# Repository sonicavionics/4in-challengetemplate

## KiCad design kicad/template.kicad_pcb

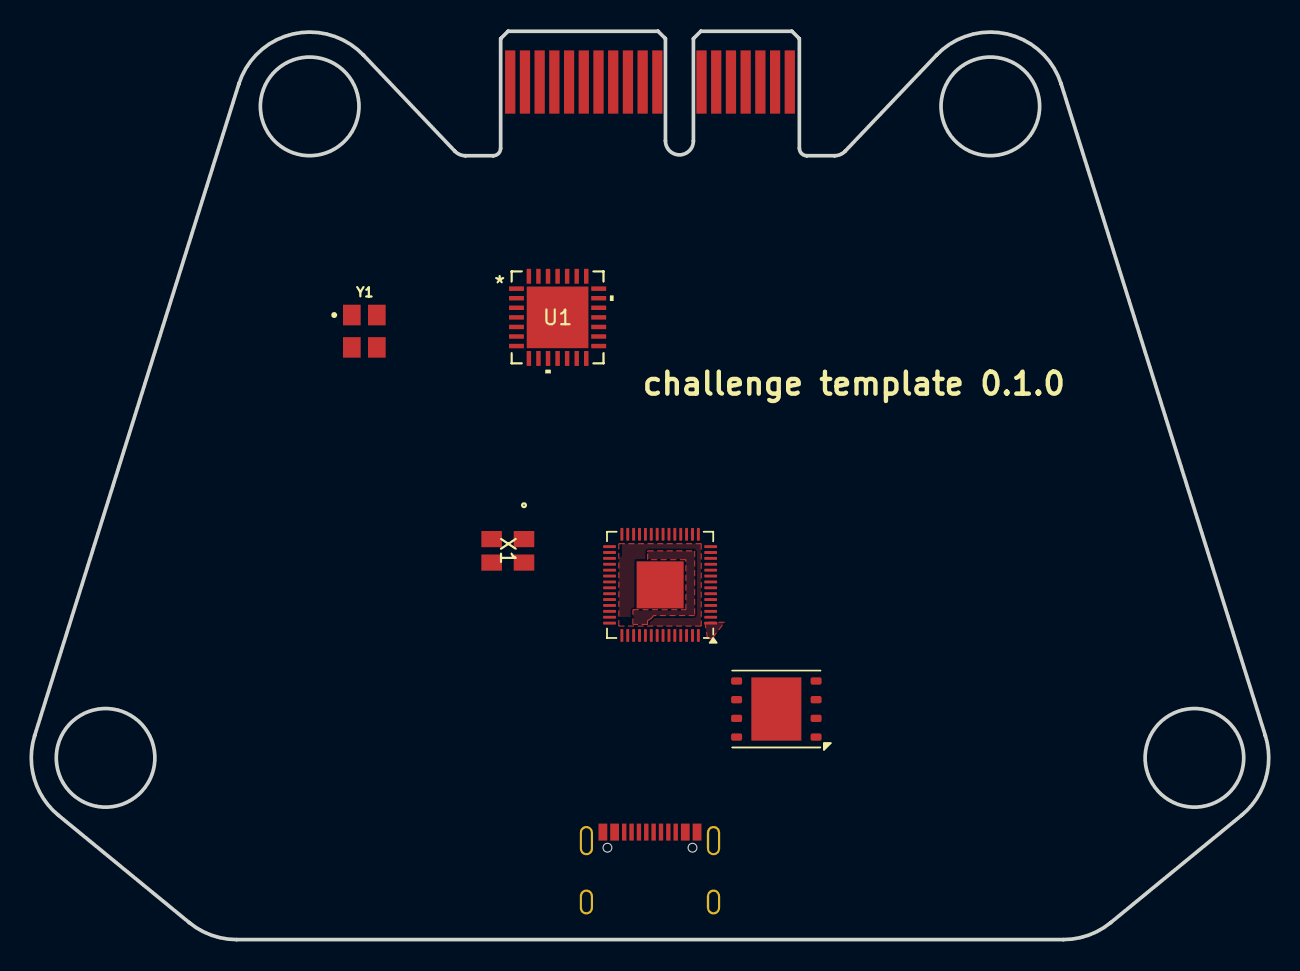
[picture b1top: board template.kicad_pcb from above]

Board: 2 copper layers, 84.1 x 61.7 mm, 7 parts (1 on the bottom side), 9 nets, no tracks yet.

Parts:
J1: Bus_PCI_Express_x1; BUS_PCIexpress_x1
J6: USB_C_Receptacle_USB2.0_16P; USB_C_Receptacle_Palconn_UTC16-G
U1: MCP25625T-E/ML; QFN28_6X6MC_MCH
U2: RP2040; QFN-56-1EP_7x7mm_P0.4mm_EP3.2x3.2mm
U4: W25Q128JVP; WSON-8-1EP_6x5mm_P1.27mm_EP3.4x4.3mm
X1: ABM8-272-T3; ABM8-272-T3_ABR
Y1: X322516MLB4SI; OSC_X322516MLB4SI

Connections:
+3.3V: J1.A9 (+3.3V), J1.A10 (+3.3V), J1.A11 (~PERST), J1.B9 (JTAG1), J1.B10 (3.3Vaux), J1.B11 (~WAKE)
+5V: J1.A12 (GND), J1.A13 (REFCLK+), J1.A14 (REFCLK-), J1.B12 (RSVD), J1.B13 (GND), J1.B14 (PETp0)
+BAT: J1.A16 (PERp0), J1.A17 (PERn0), J1.A18 (GND), J1.B16 (GND), J1.B17 (~PRSNT2), J1.B18 (GND)
GND: J1.A4 (GND), J1.A5 (JTAG2), J1.A6 (JTAG3), J1.A7 (JTAG4), J1.B1 (+12V), J1.B2 (+12V), J1.B3 (+12V), J1.B4 (GND), J1.B5 (SMCLK), J1.B6 (SMDAT), J1.B7 (GND), J6.A1 (GND), J6.A12 (GND), J6.B1 (GND), J6.B12 (GND), J6.S1 (SHIELD)
unnamed: J6.A6 (D+), J6.B6 (D+)
unnamed: J6.A7 (D-), J6.B7 (D-)
unnamed: U2.23 (DVDD), U2.50 (DVDD)
unnamed: U2.1 (IOVDD), U2.10 (IOVDD), U2.22 (IOVDD), U2.33 (IOVDD), U2.42 (IOVDD), U2.49 (IOVDD)
unnamed: Y1.2, Y1.4

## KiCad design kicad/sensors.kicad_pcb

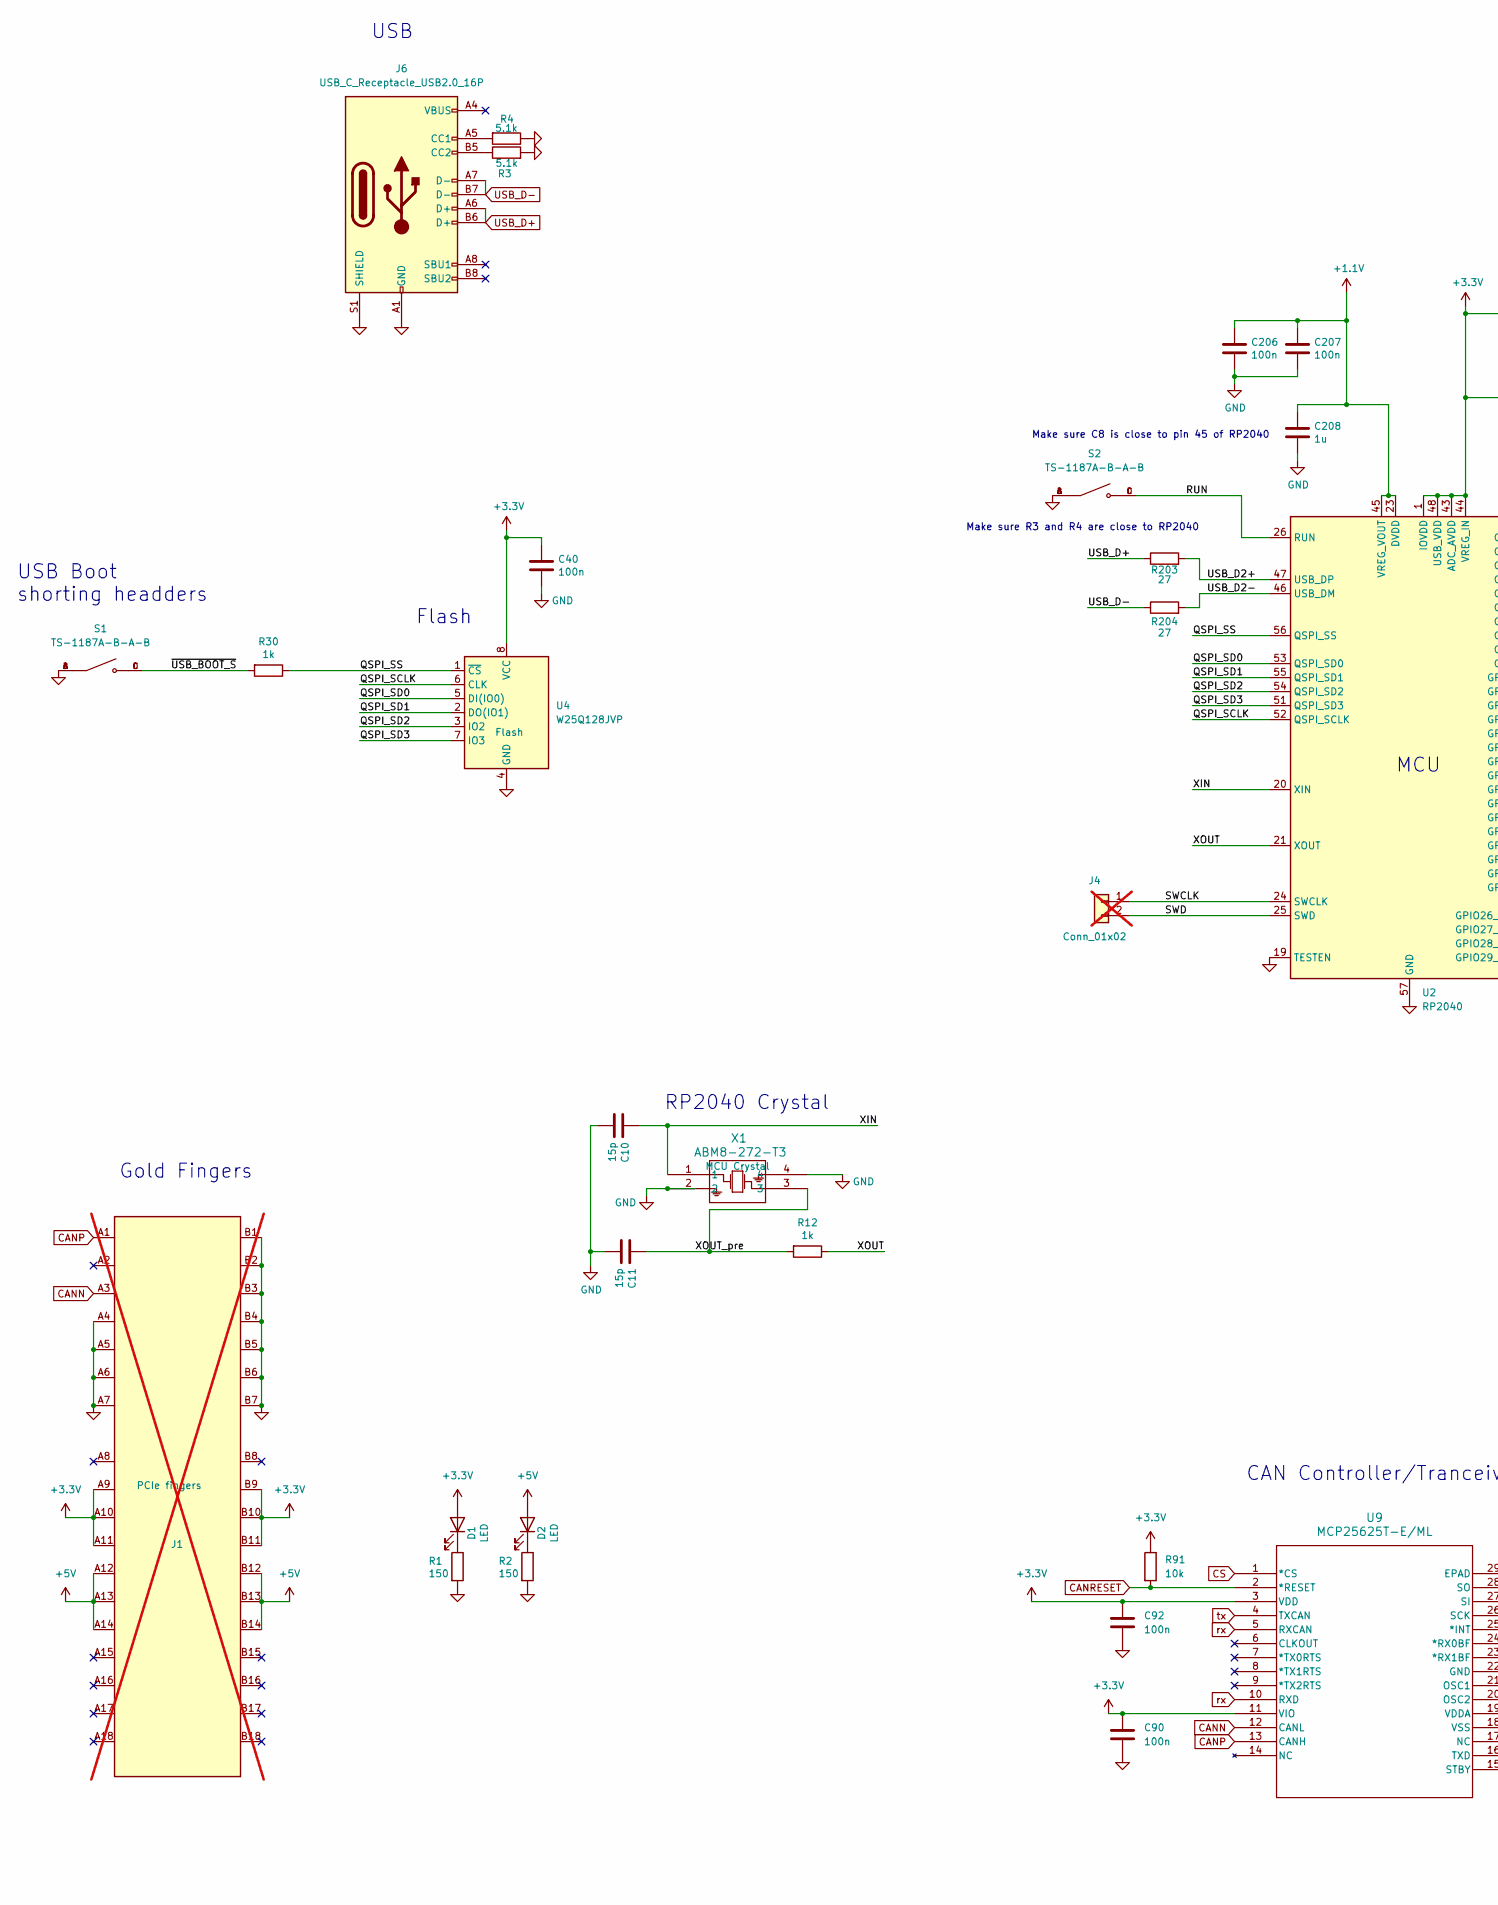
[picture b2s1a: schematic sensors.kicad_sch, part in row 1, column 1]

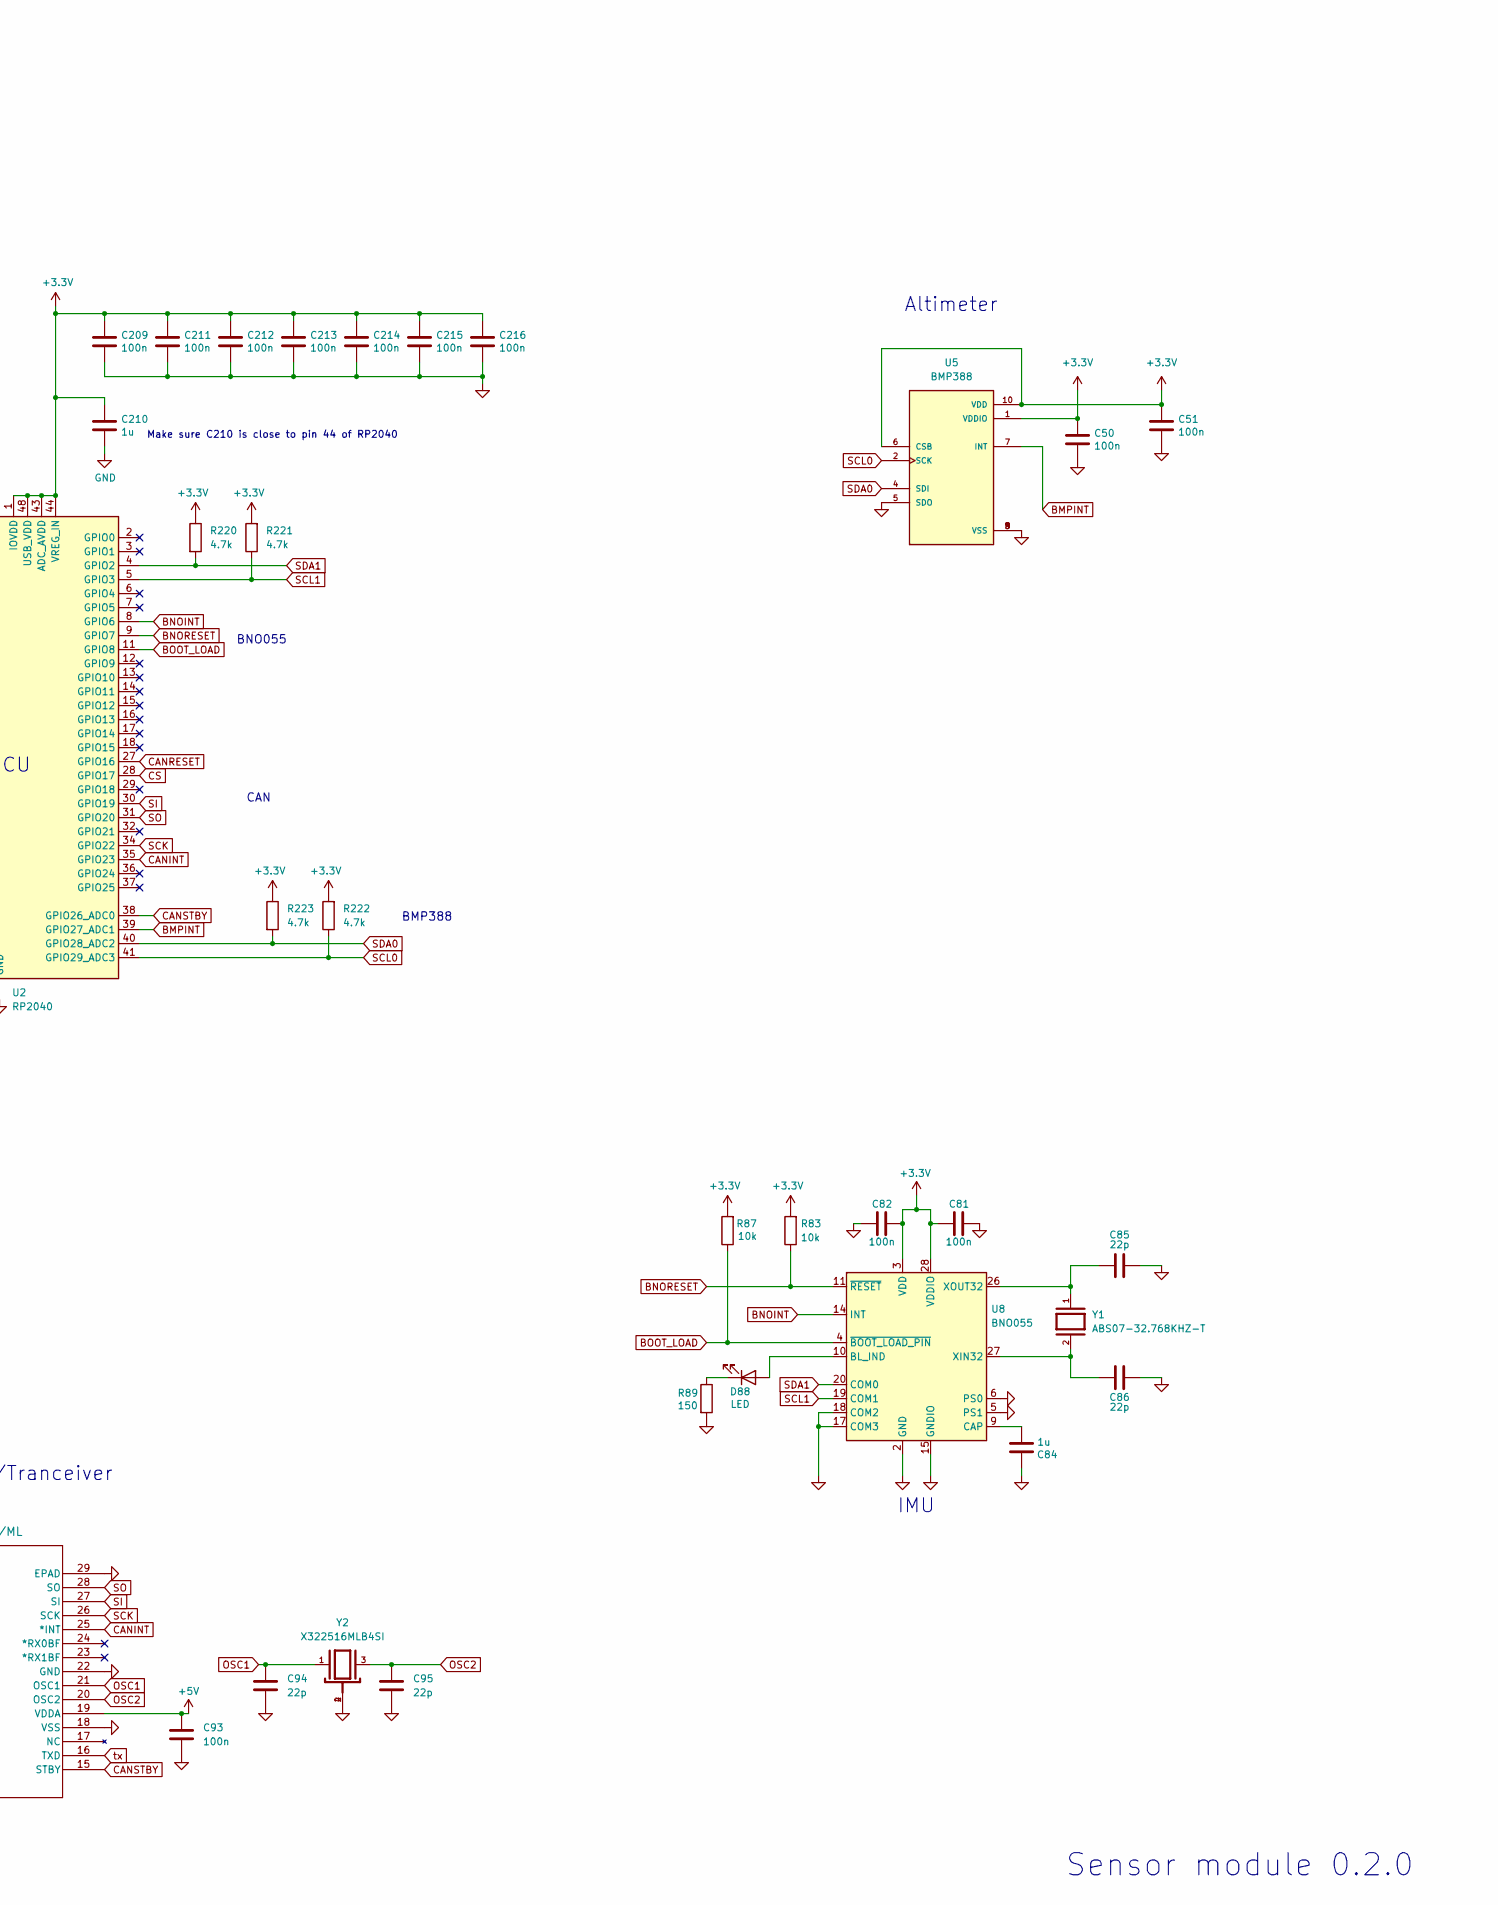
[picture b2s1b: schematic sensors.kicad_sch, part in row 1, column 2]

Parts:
C10, C11: 15p; C_0402_1005Metric; LCSC Part # C1548
C40, C50, C51, C81, C82, C90, C92, C93, C206, C207, C209, C211, C212, C213, C214, C215, C216: 100n; C_0402_1005Metric; LCSC Part # C307331
C84, C208, C210: 1u; C_0402_1005Metric; LCSC Part # C52923
C85, C86, C94, C95: 22p; C_0402_1005Metric; LCSC Part # C1555
D1, D2, D88: LED; LED_0603_1608Metric; LCSC Part # C2286
J1: Bus_PCI_Express_x1; BUS_PCIexpress_x1; LCSC Part # n/a; not fitted
J4: Conn_01x02; PinHeader_1x02_P2.54mm_Vertical; LCSC Part # n/a; not fitted
J6: USB_C_Receptacle_USB2.0_16P; USB_C_Receptacle_Palconn_UTC16-G; LCSC Part # C2765186
R1, R2, R89: 150; R_0603_1608Metric; LCSC Part # C22808
R3, R4: 5.1k; R_0402_1005Metric; LCSC Part # C25905
R12, R30: 1k; R_0402_1005Metric; LCSC Part # C11702
R83, R87, R91: 10k; R_0402_1005Metric; LCSC Part # C25744
R203, R204: 27; R_0402_1005Metric; LCSC Part # C25100
R220, R221, R222, R223: 4.7k; R_0402_1005Metric; LCSC Part # C25900
S1, S2: TS-1187A-B-A-B; SW_TS-1187A-B-A-B; PARTREV A0; LCSC Part # C318884
U2: RP2040; QFN-56-1EP_7x7mm_P0.4mm_EP3.2x3.2mm; LCSC C2040
U4: W25Q128JVP; WSON-8-1EP_6x5mm_P1.27mm_EP3.4x4.3mm; LCSC C190862
U5: BMP388; PQFN50P200X200X80-10N; PARTREV 1.1; LCSC Part # C779278
U8: BNO055; LGA-28_5.2x3.8mm_P0.5mm; LCSC C93216
U9: MCP25625T-E/ML; QFN28_6X6MC_MCH; LCSC Part # C191253
X1: ABM8-272-T3; ABM8-272-T3_ABR; LCSC Part # C20625731
Y1: ABS07-32.768KHZ-T; XTAL_ABS07-32.768KHZ-T; PARTREV 08.19.15; LCSC Part # C130253
Y2: X322516MLB4SI; OSC_X322516MLB4SI; PARTREV N/A; LCSC Part # C12668

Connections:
+1.1V: C206.1, C207.1, C208.1, U2.23 (DVDD), U2.45 (VREG_VOUT), U2.50 (DVDD)
+3.3V: C40.1, C50.1, C51.1, C81.1, C82.2, C90.1, C92.1, C209.1, C210.1, C211.1, C212.1, C213.1, C214.1, C215.1, C216.1, D1.2 (A), J1.A9 (+3.3V), J1.A10 (+3.3V), J1.A11 (~PERST), J1.B9 (JTAG1), J1.B10 (3.3Vaux), J1.B11 (~WAKE), R83.2, R87.2, R91.1, R220.1, R221.2, R222.2, R223.1, U2.1 (IOVDD), U2.10 (IOVDD), U2.22 (IOVDD), U2.33 (IOVDD), U2.42 (IOVDD), U2.43 (ADC_AVDD), U2.44 (VREG_IN), U2.48 (USB_VDD), U2.49 (IOVDD), U4.8 (VCC), U5.1 (VDDIO), U5.6 (CSB), U5.10 (VDD), U8.3 (VDD), U8.28 (VDDIO), U9.3 (VDD), U9.11 (VIO)
+5V: C93.1, D2.2 (A), J1.A12 (GND), J1.A13 (REFCLK+), J1.A14 (REFCLK-), J1.B12 (RSVD), J1.B13 (GND), J1.B14 (PETp0), U9.19 (VDDA)
/QSPI_SCLK: U2.52 (QSPI_SCLK), U4.6 (CLK)
/QSPI_SD0: U2.53 (QSPI_SD0), U4.5 (DI(IO0))
/QSPI_SD1: U2.55 (QSPI_SD1), U4.2 (DO(IO1))
/QSPI_SD2: U2.54 (QSPI_SD2), U4.3 (IO2)
/QSPI_SD3: U2.51 (QSPI_SD3), U4.7 (IO3)
/QSPI_SS: R30.1, U2.56 (QSPI_SS), U4.1 (~CS)
/RUN: S2.C, S2.D, U2.26 (RUN)
/SWCLK: J4.1, U2.24 (SWCLK)
/SWD: J4.2, U2.25 (SWD)
/USB_D2+: R203.2, U2.47 (USB_DP)
/USB_D2-: R204.2, U2.46 (USB_DM)
/XIN: C10.1, U2.20 (XIN), X1.1
/XOUT: R12.1, U2.21 (XOUT)
/XOUT_pre: C11.1, R12.2, X1.3
/~USB_BOOT_S: R30.2, S1.C, S1.D
BMPINT: U2.39 (GPIO27_ADC1), U5.7 (INT)
BNOINT: U2.8 (GPIO6), U8.14 (INT)
BNORESET: R83.1, U2.9 (GPIO7), U8.11 (~RESET)
BOOT_LOAD: R87.1, U2.11 (GPIO8), U8.4 (~BOOT_LOAD_PIN)
CANINT: U2.35 (GPIO23), U9.25 (*INT)
CANN: J1.A3 (+12V), U9.12 (CANL)
CANP: J1.A1 (~PRSNT1), U9.13 (CANH)
CANRESET: R91.2, U2.27 (GPIO16), U9.2 (*RESET)
CANSTBY: U2.38 (GPIO26_ADC0), U9.15 (STBY)
CS: U2.28 (GPIO17), U9.1 (*CS)
GND: C10.2, C11.2, C40.2, C50.2, C51.2, C81.2, C82.1, C84.1, C85.2, C86.1, C90.2, C92.2, C93.2, C94.2, C95.2, C206.2, C207.2, C208.2, C209.2, C210.2, C211.2, C212.2, C213.2, C214.2, C215.2, C216.2, J1.A4 (GND), J1.A5 (JTAG2), J1.A6 (JTAG3), J1.A7 (JTAG4), J1.B1 (+12V), J1.B2 (+12V), J1.B3 (+12V), J1.B4 (GND), J1.B5 (SMCLK), J1.B6 (SMDAT), J1.B7 (GND), J6.A1 (GND), J6.A12 (GND), J6.B1 (GND), J6.B12 (GND), J6.S1 (SHIELD), R1.2, R2.2, R3.2, R4.1, R89.2, S1.A, S1.B, S2.A, S2.B, U2.19 (TESTEN), U2.57 (GND), U4.4 (GND), U5.3 (VSS), U5.5 (SDO), U5.8 (VSS), U5.9 (VSS), U8.2 (GND), U8.5 (PS1), U8.6 (PS0), U8.15 (GNDIO), U8.16 (GNDIO), U8.17 (COM3), U8.18 (COM2), U8.25 (GNDIO), U9.18 (VSS), U9.22 (GND), U9.29 (EPAD), X1.2, X1.4, Y2.2, Y2.4
unnamed: D1.1 (K), R1.1
unnamed: D2.1 (K), R2.1
unnamed: D88.2 (A), U8.10 (BL_IND)
unnamed: D88.1 (K), R89.1
unnamed: J6.A5 (CC1), R4.2
unnamed: J6.B5 (CC2), R3.1
unnamed: C84.2, U8.9 (CAP)
unnamed: C86.2, U8.27 (XIN32), Y1.2
unnamed: C85.1, U8.26 (XOUT32), Y1.1
OSC1: C94.1, U9.21 (OSC1), Y2.1
OSC2: C95.1, U9.20 (OSC2), Y2.3
SCK: U2.34 (GPIO22), U9.26 (SCK)
SCL0: R222.1, U2.41 (GPIO29_ADC3), U5.2 (SCK)
SCL1: R221.1, U2.5 (GPIO3), U8.19 (COM1)
SDA0: R223.2, U2.40 (GPIO28_ADC2), U5.4 (SDI)
SDA1: R220.2, U2.4 (GPIO2), U8.20 (COM0)
SI: U2.30 (GPIO19), U9.27 (SI)
SO: U2.31 (GPIO20), U9.28 (SO)
USB_D+: J6.A6 (D+), J6.B6 (D+), R203.1
USB_D-: J6.A7 (D-), J6.B7 (D-), R204.1
rx: U9.5 (RXCAN), U9.10 (RXD)
tx: U9.4 (TXCAN), U9.16 (TXD)

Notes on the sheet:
Make sure C210 is close to pin 44 of RP2040
Make sure C8 is close to pin 45 of RP2040
RP2040 Crystal
Altimeter
BNO055
BMP388
IMU
USB
Make sure R3 and R4 are close to RP2040
CAN
USB Boot shorting headders
Sensor module 0.2.0
Gold Fingers
MCU
CAN Controller/Tranceiver
Flash

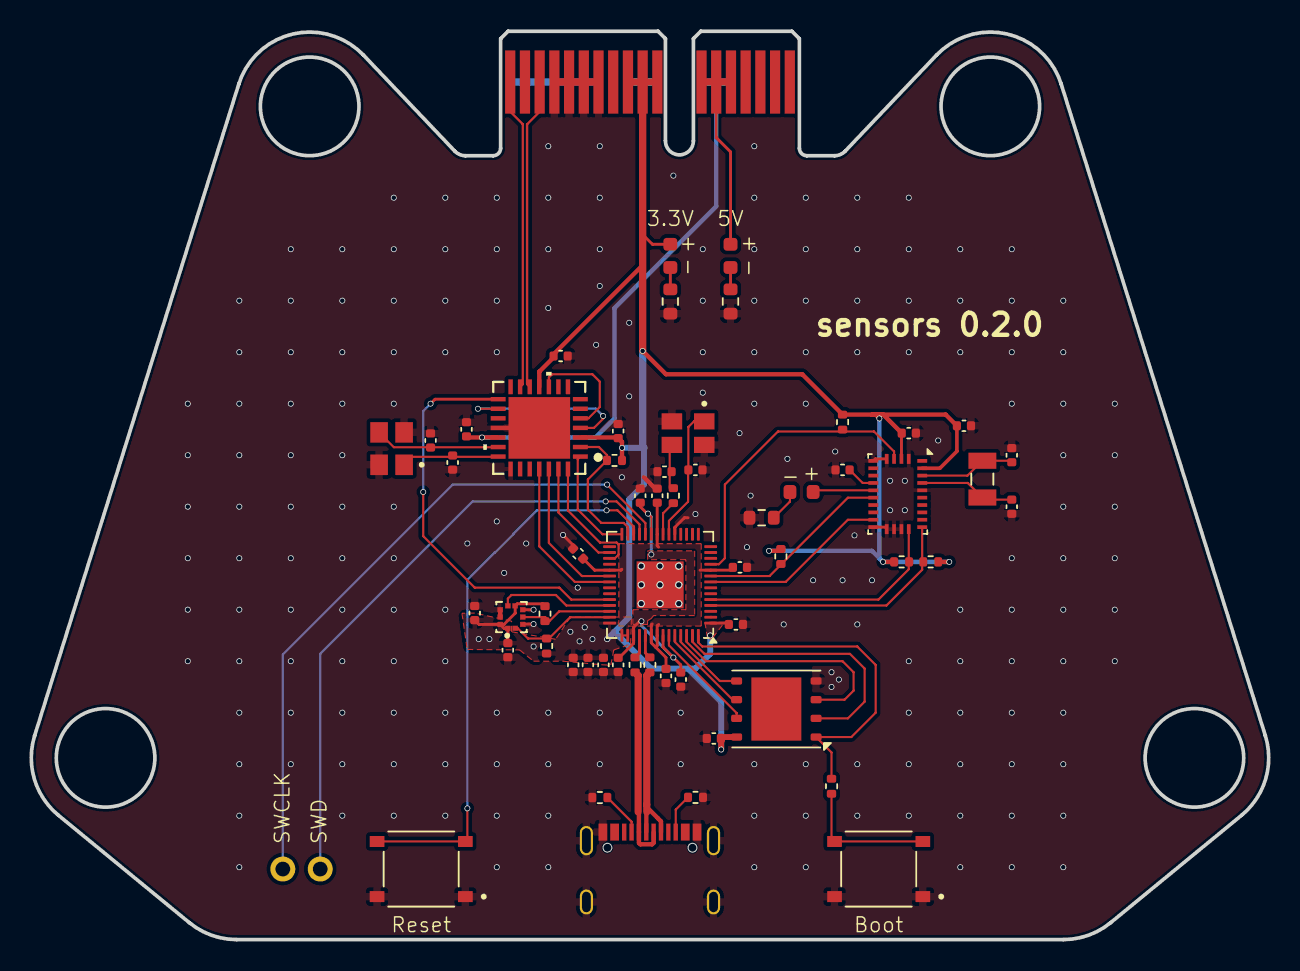
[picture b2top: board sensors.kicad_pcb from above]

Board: 2 copper layers, 84.1 x 61.7 mm, 58 parts (1 on the bottom side), 51 nets.

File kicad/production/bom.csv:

Designator,Footprint,Quantity,Value,LCSC Part #
"C10, C11",0402,2,15p,C1548
"C206, C207, C209, C211, C212, C213, C214, C215, C216, C40, C50, C51, C81, C82, C90, C92, C93",0402,17,100n,C307331
"C208, C210, C84",0402,3,1u,C52923
"C85, C86, C94, C95",0402,4,22p,C1555
"D1, D2, D88",0603,3,LED,C2286
J6,USB_C_Receptacle_Palconn_UTC16-G,1,USB_C_Receptacle_USB2.0_16P,C2765186
"R1, R2, R89",0603,3,150,C22808
"R12, R30",0402,2,1k,C11702
"R203, R204",0402,2,27,C25100
"R220, R221, R222, R223",0402,4,4.7k,C25900
"R3, R4",0402,2,5.1k,C25905
"R83, R87, R91",0402,3,10k,C25744
"S1, S2",SW_TS-1187A-B-A-B,2,TS-1187A-B-A-B,C318884
U2,QFN-56-1EP_7x7mm_P0.4mm_EP3.2x3.2mm,1,RP2040,C2040
U4,WSON-8-1EP_6x5mm_P1.27mm_EP3.4x4.3mm,1,W25Q128JVP,C190862
U5,PQFN50P200X200X80-10N,1,BMP388,C779278
U8,LGA-28_5.2x3.8mm_P0.5mm,1,BNO055,C93216
U9,QFN28_6X6MC_MCH,1,MCP25625T-E/ML,C191253
X1,ABM8-272-T3_ABR,1,ABM8-272-T3,C20625731
Y1,XTAL_ABS07-32.768KHZ-T,1,ABS07-32.768KHZ-T,C130253
Y2,OSC_X322516MLB4SI,1,X322516MLB4SI,C12668

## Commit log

2025-01-21 init
2025-01-21 Auto-exported schematic, PCB, and 3D model
2025-02-16 refactor libraries
2025-02-16 Update images
2025-03-03 update to kicad 9, and delete everything from PCB editor
2025-05-06 Remove *.kicad_prl and add to gitignore
